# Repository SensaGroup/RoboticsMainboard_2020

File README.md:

# SENSA - Robotics_Mainboard

SENSA Mainboard is used on the Eurobot 2020 competition.

## Description
The Mainboard is the commander of the robot system. 
We used an Arduino Mega for the base and we developed the extension board

## Features
- 5V/5VA/12V inputs with protection
- 2 Sockets for stepper drivers, based on the A4988 pinout
- 6x servo pinouts with external 5V power supply
- 6x 12V pneumatic valve controller
- 5x 1AMP relays 
- AX-12 support
- 6x optoisolated 12V infrared sensor inputs
- 6x binary 5V sensor inputs
- NRF24L01
- I2C/UART pinouts

## Software
All software is written in C for AVR.
View README in the Software folder.

## Pictures

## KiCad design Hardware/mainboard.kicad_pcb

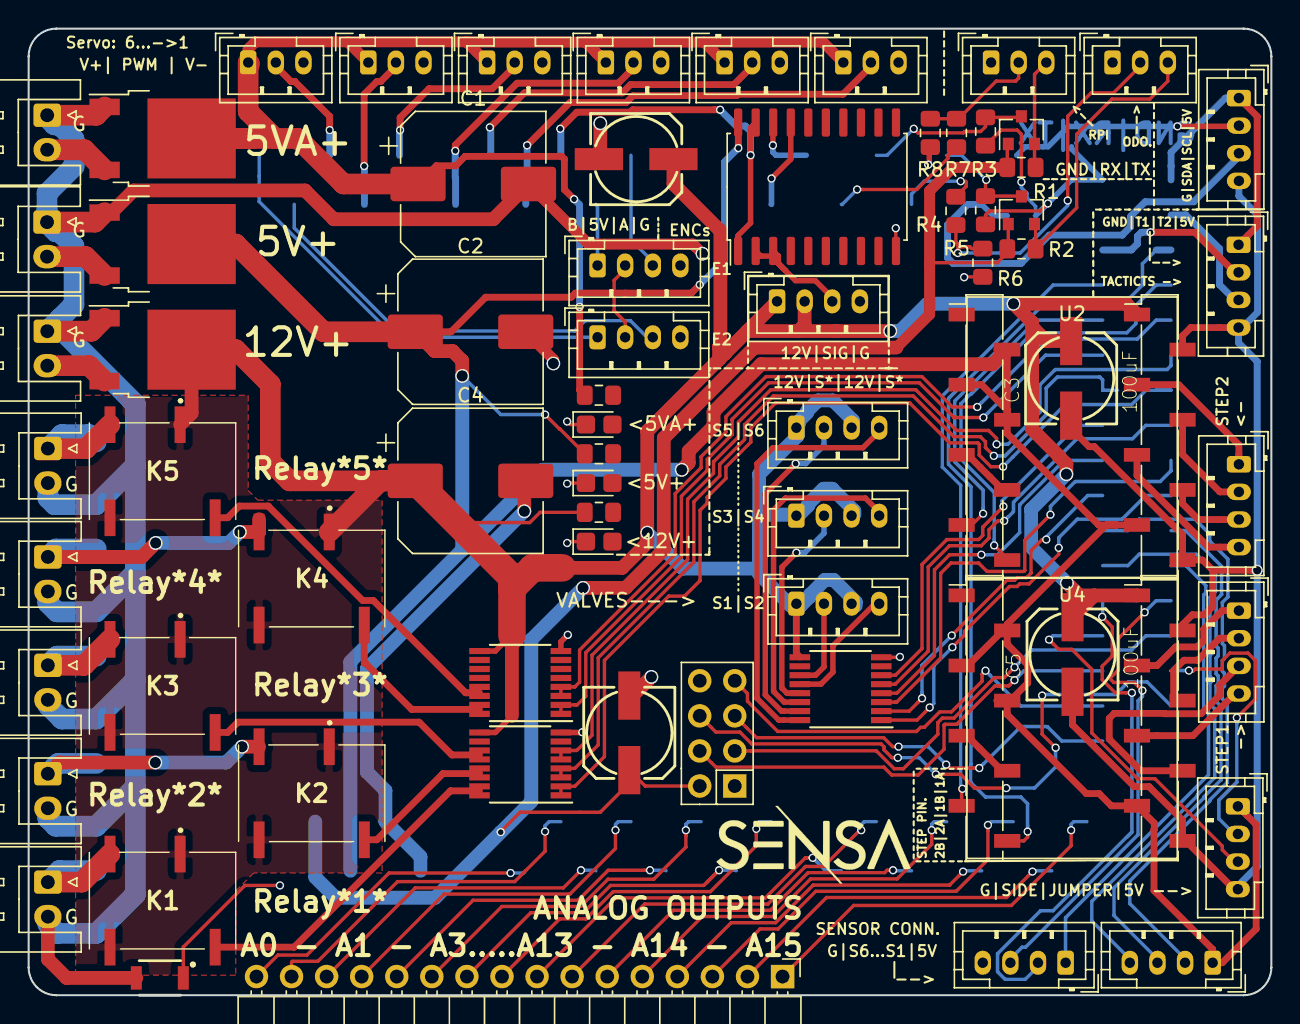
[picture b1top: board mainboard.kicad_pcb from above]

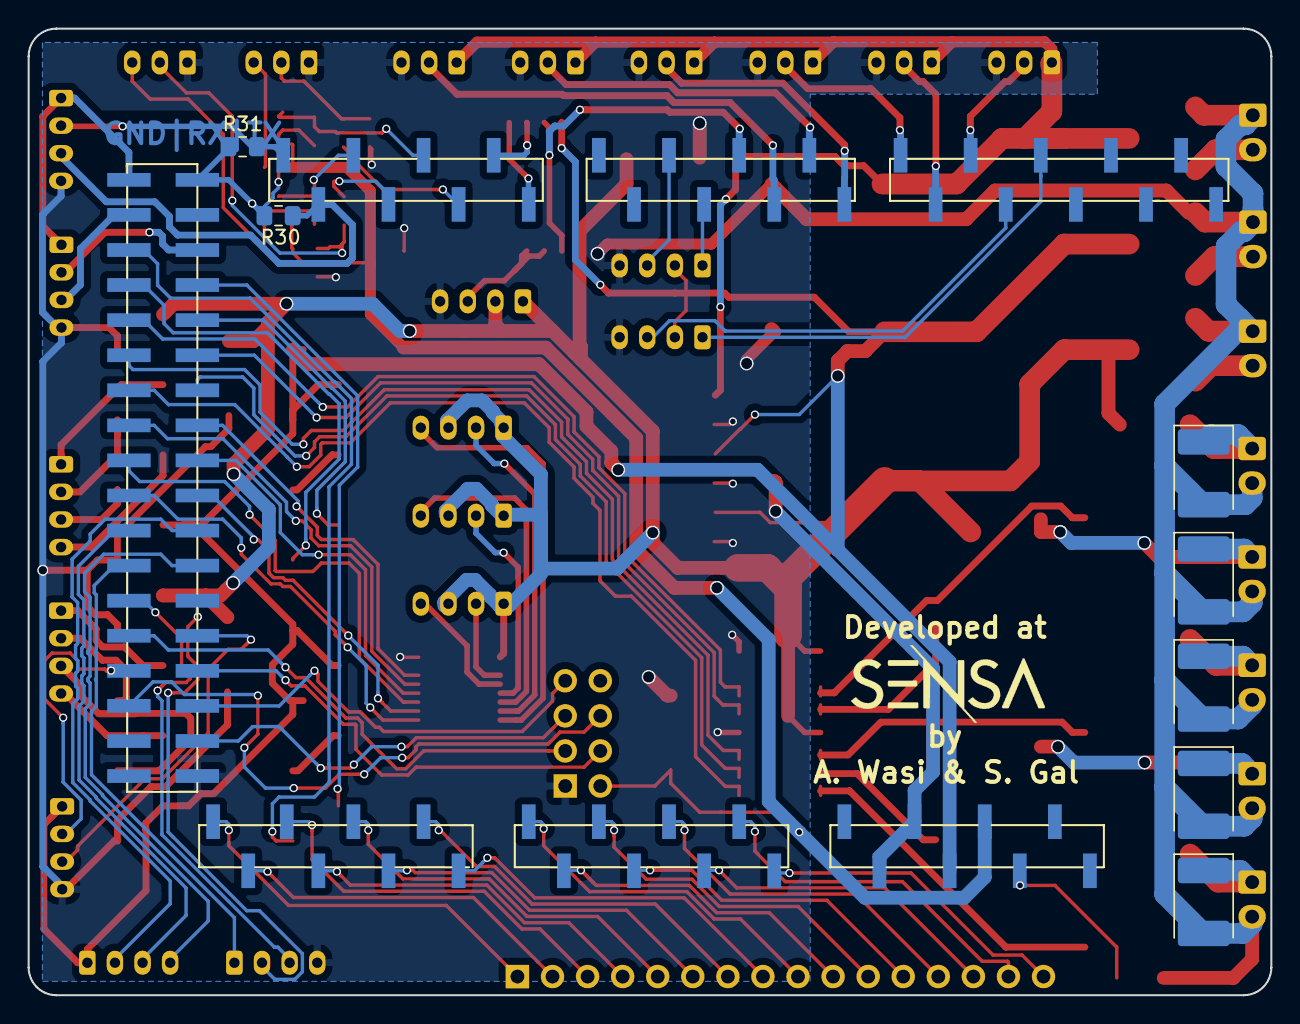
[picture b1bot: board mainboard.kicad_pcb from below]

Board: 2 copper layers, 90.0 x 70.0 mm, 79 parts (7 on the bottom side), 110 nets.

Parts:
5V+, 5VA+, 12V+: JST_XH; JST_XH_S2B-XH-A_1x02_P2.50mm_Horizontal
12V|S*|12V|S*: VALVE; JST_PH_B4B-PH-K_1x04_P2.00mm_Vertical
B|5V|A|G: ENCODER 1; JST_PH_B4B-PH-K_1x04_P2.00mm_Vertical
C1, C2, C4: 470uF; CP_Elec_10x10
C3, C5, C8, C13: 100uF; CAPAE0607X600N
D1, D2, D4, D7, D8: D; D_2114_3652Metric_Pad1.85x3.75mm_HandSolder
D3, D5, D6: LED; LED_0805_2012Metric_Castellated
G: RConn_JST_90DEG; JST_XH_S2B-XH-A_1x02_P2.50mm_Horizontal
G#2, G#3, G#4, G#5: RConn_JST_90DEG; JST_XH_S2B-XH-A_1x02_P2.50mm_Horizontal
J2: AX; JST_PH_B4B-PH-K_1x04_P2.00mm_Vertical
J3: Conn_01x16; PinHeader_1x16_P2.54mm_Horizontal
J7: VALVE; JST_PH_B4B-PH-K_1x04_P2.00mm_Vertical
J9: SERVO5; JST_PH_B3B-PH-K_1x03_P2.00mm_Vertical
J10: SIDE_SWITCH; JST_PH_B4B-PH-K_1x04_P2.00mm_Vertical
J12: TACTIC_SWITCH; JST_PH_B4B-PH-K_1x04_P2.00mm_Vertical
J13: DISPLAY_CON; JST_PH_B4B-PH-K_1x04_P2.00mm_Vertical
J14: RPI_COM; JST_PH_B3B-PH-K_1x03_P2.00mm_Vertical
J16, J17: SENSOR_IN; JST_PH_B4B-PH-K_1x04_P2.00mm_Vertical
J18: ODO_COM; JST_PH_B3B-PH-K_1x03_P2.00mm_Vertical
J19: SERVO1; JST_PH_B3B-PH-K_1x03_P2.00mm_Vertical
J20: SERVO2; JST_PH_B3B-PH-K_1x03_P2.00mm_Vertical
J21: SERVO6; JST_PH_B3B-PH-K_1x03_P2.00mm_Vertical
J30: ENCODER 1; JST_PH_B4B-PH-K_1x04_P2.00mm_Vertical
J32, J36: STEPPER_OUT; JST_PH_B4B-PH-K_1x04_P2.00mm_Vertical
J33: SERVO3; JST_PH_B3B-PH-K_1x03_P2.00mm_Vertical
J34: SERVO4; JST_PH_B3B-PH-K_1x03_P2.00mm_Vertical
K1, K2, K3, K4, K5: G6L-1F-TR-DC12; G6L1FTRDC5
NT1, NT2: NetTie; NetTie-2_SMD_Pad0.5mm
Q1, Q2, Q5: DMP2100U; TO-252-2
Q3, Q4: BSS138; SOT-23
R1, R2, R3, R4, R5, R7: 10K; R_0805_2012Metric_Pad1.15x1.40mm_HandSolder
R6, R8: 20K; R_0805_2012Metric_Pad1.15x1.40mm_HandSolder
R28, R29, R33: 1K; R_0805_2012Metric_Pad1.15x1.40mm_HandSolder
R30, R31: 4k7; R_0805_2012Metric_Pad1.15x1.40mm_HandSolder
RESET1: SW_Push; B3U-1000P
S1,S2: VALVE; JST_PH_B4B-PH-K_1x04_P2.00mm_Vertical
U1, U6, U7: ULN2003A; TSSOP-16_4.4x5mm_P0.65mm
U2, U4: A4988_STEPPER_MODULE; STEP_SMD
U3: NRF24L01_Breakout; PinSocket_2x04_P2.54mm_Vertical
U5: 74LS241; SOIC-20W_7.5x12.8mm_P1.27mm
XA1: Arduino_Mega2560_Shield

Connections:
1A1: J36.4, U4.12
1A2: J32.4, U2.12
1B1: J36.3, U4.11
1B2: J32.3, U2.11
2A1: J36.2, U4.13
2A2: J32.2, U2.13
2B1: J36.1, U4.14
2B2: J32.1, U2.14
+3V3: C13.+, Q3.1, Q4.1, R1.1, R2.1, U3.2, XA1.3V3
+5V: B|5V|A|G.2, C2.1, J10.1, J12.1, J13.1, J30.2, Q1.2, R3.1, R4.1, R29.2, R30.1, R31.1, U2.2, U2.3, U2.4, U2.10, U4.2, U4.3, U4.4, U4.10, U5.20, XA1.5V1, XA1.5V3, XA1.5V4
+5VA: C1.1, J9.1, J16.1, J19.1, J20.1, J21.1, J33.1, J34.1, Q2.2, R33.2
+12V: 12V|S*|12V|S*.1, 12V|S*|12V|S*.3, C3.+, C4.1, C5.+, C8.+, J2.1, J2.2, J7.1, J7.3, K1.2, K1.5, K2.2, K2.5, K3.2, K3.5, K4.2, K4.5, K5.2, K5.5, Q5.2, R28.2, S1,S2.1, S1,S2.3, U1.9, U2.16, U4.16, U6.9, U7.9
A1: B|5V|A|G.3, XA1.D2
A2: J30.3, XA1.D11
AX_CONTROL: U5.1, U5.19, XA1.D4
AX_RX: U5.18, XA1.D15
AX_SIGNAL: J2.3, U5.2, U5.3
AX_TX: U5.17, XA1.D14
B1: B|5V|A|G.1, XA1.D3
B2: J30.1, XA1.D12
CE: U3.3, XA1.D47
CS: U3.4, XA1.D48
DIR1: U4.8, XA1.D25
DIR2: U2.8, XA1.D27
GND: 5V+.1, 5VA+.1, 12V+.1, B|5V|A|G.4, C1.2, C2.2, C3.-, C4.2, C5.-, C8.-, C13.-, D1.2, D2.2, D3.1, D4.2, D5.1, D6.1, D7.2, D8.2, G.2, G#2.2, G#3.2, G#4.2, G#5.2, J2.4, J9.3, J10.4, J12.4, J13.4, J14.1, J17.4, J18.1, J19.3, J20.3, J21.3, J30.4, J33.3, J34.3, Q1.1, Q2.1, Q5.1, R6.2, R8.2, RESET1.2, U1.8, U2.9, U2.15, U3.1, U4.9, U4.15, U5.10, U6.8, U7.8, XA1.GND1, XA1.GND2, XA1.GND3, XA1.GND5, XA1.GND6
JUMPER: J10.2, XA1.D49
MISO: U3.7, XA1.D50
MOSI: U3.6, XA1.D51
unnamed: D1.1, G#4.1, K1.4
unnamed: D2.1, G.1, K4.4
unnamed: D3.2, R28.1
unnamed: D4.1, G#2.1, K3.4
unnamed: D5.2, R29.1
unnamed: D6.2, R33.1
unnamed: D7.1, G#3.1, K2.4
unnamed: D8.1, G#5.1, K5.4
unnamed: J3.1, XA1.A15
unnamed: J3.2, XA1.A14
unnamed: J3.3, XA1.A13
unnamed: J3.4, XA1.A12
unnamed: J3.5, XA1.A11
unnamed: J3.6, XA1.A10
unnamed: J3.7, XA1.A9
unnamed: J3.8, XA1.A8
unnamed: J3.9, XA1.A7
unnamed: J3.10, XA1.A6
unnamed: J3.11, XA1.A5
unnamed: J3.12, XA1.A4
unnamed: J3.13, XA1.A3
unnamed: J3.14, XA1.A2
unnamed: J3.15, XA1.A1
unnamed: J3.16, XA1.A0
unnamed: 5VA+.2, Q2.3
unnamed: 5V+.2, Q1.3
unnamed: 12V+.2, Q5.3
unnamed: NT1.1, U4.5
unnamed: NT1.2, U4.6
unnamed: NT2.1, U2.5
unnamed: NT2.2, U2.6
ODO_RX_HIGH: R5.1, XA1.D18
ODO_RX_LOW: J18.2, R5.2, R6.1
ODO_TX_HIGH: Q4.3, R4.2, XA1.D19
ODO_TX_LOW: J18.3, Q4.2, R2.2
PWM1: J19.2, XA1.D5
PWM2: J20.2, XA1.D6
PWM3: J33.2, XA1.D7
PWM4: J34.2, XA1.D8
PWM5: J9.2, XA1.D9
PWM6: J21.2, XA1.D10
R1_CONT: U1.1, U1.2, XA1.D33
R1_SIG: K1.8, U1.15, U1.16
R2_CONT: U1.3, U1.4, XA1.D32
R2_SIG: K2.8, U1.13, U1.14
R3_CONT: U1.5, U1.6, XA1.D31
R3_SIG: K3.8, U1.11, U1.12
R4_CONT: U6.1, U6.2, XA1.D30
R4_SIG: K4.8, U6.15, U6.16
R5_CONT: U6.3, U6.4, XA1.D29
R5_SIG: K5.8, U6.13, U6.14
RPI_RX_HIGH: R7.1, XA1.D16
RPI_RX_LOW: J14.2, R7.2, R8.1
RPI_TX_HIGH: Q3.3, R3.2, XA1.D17
RPI_TX_LOW: J14.3, Q3.2, R1.2
RST: RESET1.1, XA1.RST1
SCK: U3.5, XA1.D52
SCL: J13.2, R31.2, XA1.D21
SDA: J13.3, R30.2, XA1.D20
SENSOR1: J16.2, XA1.D40
SENSOR2: J16.3, XA1.D41
SENSOR3: J16.4, XA1.D42
SENSOR4: J17.1, XA1.D43
SENSOR5: J17.2, XA1.D44
SENSOR6: J17.3, XA1.D45
SIDE: J10.3, XA1.D46
STEP1: U4.7, XA1.D26
STEP2: U2.7, XA1.D28
TACTIC1: J12.3, XA1.D23
TACTIC2: J12.2, XA1.D24
_S1: S1,S2.2, U7.11
_S1_SIG: U7.6, XA1.D34
_S2: S1,S2.4, U7.12
_S2_SIG: U7.5, XA1.D35
_S3: J7.2, U7.13
_S3_SIG: U7.4, XA1.D36
_S4: J7.4, U7.14
_S4_SIG: U7.3, XA1.D37
_S5: 12V|S*|12V|S*.2, U7.15
_S5_SIG: U7.2, XA1.D38
_S6: 12V|S*|12V|S*.4, U7.16
_S6_SIG: U7.1, XA1.D39

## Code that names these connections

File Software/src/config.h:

#include <Arduino.h>

#ifndef CONFIG_H
#define CONFIG_H

#define RELAY_PIN_1             33 
#define RELAY_PIN_2             32
#define RELAY_PIN_3             31
#define RELAY_PIN_4             30
#define RELAY_PIN_5             29

#define STEPPER_PIN_STEP_1      26
#define STEPPER_PIN_DIR_1       25
#define STEPPER_PIN_STEP_2      28
#define STEPPER_PIN_DIR_2       27

#define SERVO_PIN_1             5
#define SERVO_PIN_2             6
#define SERVO_PIN_3             7
#define SERVO_PIN_4             8
#define SERVO_PIN_5             9
#define SERVO_PIN_6             10
// SERVO START UP POSITION - gets executed at init
#define SERVO_SUP_1             0 
#define SERVO_SUP_2             0 
#define SERVO_SUP_3             0 
#define SERVO_SUP_4             0 
#define SERVO_SUP_5             0 
#define SERVO_SUP_6             0 


#define VALVE_PIN_1             34 
#define VALVE_PIN_2             35
#define VALVE_PIN_3             36
#define VALVE_PIN_4             37
#define VALVE_PIN_5             38
#define VALVE_PIN_6             39

#define SENSOR_PIN_1            40 
#define SENSOR_PIN_2            41
#define SENSOR_PIN_3            42
#define SENSOR_PIN_4            43
#define SENSOR_PIN_5            44
#define SENSOR_PIN_6            45
#define SENSOR_FRONT_LEFT       SENSOR_PIN_1
#define SENSOR_FRONT_CENTER     SENSOR_PIN_2
#define SENSOR_FRONT_RIGHT      SENSOR_PIN_3
#define SENSOR_BACK_LEFT        SENSOR_PIN_4
#define SENSOR_BACK_CENTER      SENSOR_PIN_5
#define SENSOR_BACK_RIGHT       SENSOR_PIN_6
#define SENSOR_DETECTION_LEVEL  1 // the status read at detection

#define ENCODER1_PIN_A          2 
#define ENCODER1_PIN_B          3
#define ENCODER2_PIN_A          11
#define ENCODER2_PIN_B          12 

#define JUMPER_PIN              49
#define TACTIC1_PIN             23
#define TACTIC2_PIN             24
#define SIDE_PIN                46

#define AX_CONTROL_PIN          4
#define AX_BAUDRATE             (1000000ul)
#define AX_ID_1                 1
#define AX_ID_2                 2
#define AX_ID_3                 3
#define AX_ID_4                 4
#define AX_SUP_1                0
#define AX_SUP_2                0 
#define AX_SUP_3                0
#define AX_SUP_4                0

#define NRF_PIN_CS              48
#define NRF_PIN_CE              47

#define ADC_PIN_0               A0
#define ADC_PIN_1               A1
#define ADC_PIN_2               A2
#define ADC_PIN_3               A3
#define ADC_PIN_4               A4
#define ADC_PIN_5               A5
#define ADC_PIN_6               A6
#define ADC_PIN_7               A7
#define ADC_PIN_8               A8
#define ADC_PIN_9               A9
#define ADC_PIN_10              A10
#define ADC_PIN_11              A11
#define ADC_PIN_12              A12
#define ADC_PIN_13              A13
#define ADC_PIN_14              A14
#define ADC_PIN_15              A15

#define YELLOW 1
#define PURPLE 0
#define TABLE1 1
#define TABLE2 0

// DEBUG SERIAL -> Serial
// ODOMETRY SERIAL -> Serial1
// RPI SERIAL -> Serial2
// AX SERIAL -> Serial3

#endif

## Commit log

2020-03-03 first
2020-03-03 eto ti sili fin.
2020-03-03 Cleanup from old unsused stuff
2020-03-03 Added config.h, this is where all the config goes
2020-03-03 config full of pins
2020-03-03 compiling with other files config.h
2020-03-03 fixed serial port on odometry.cpp
2020-03-03 added servo functionality with SUP
2020-03-03 added relay functionality
2020-03-03 added sensor detection
2020-03-03 getting errors for goto.h
2020-03-03 fixed error at gotos.h
2020-03-03 added ax
2020-03-03 added functions to ax
2020-03-03 Sorry sili, evo to bi trebalo to da bude
